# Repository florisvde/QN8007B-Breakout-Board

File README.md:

# QN8007B-Breakout-Board
Breakout board for the Quintic QN8007B single-chip stereo FM transmitter with RDS.

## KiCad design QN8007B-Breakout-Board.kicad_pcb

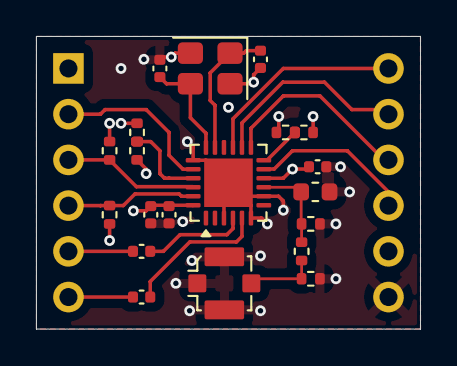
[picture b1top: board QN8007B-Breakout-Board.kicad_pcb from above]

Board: 4 copper layers, 21.3 x 16.3 mm, 22 parts (0 on the bottom side), 19 nets.

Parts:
C1: 10u; C_0402_1005Metric
C2, C7: 100n; C_0402_1005Metric
C3, C4: 10p; C_0402_1005Metric
C5, C6: 4u7; C_0402_1005Metric
J1: U.FL; U.FL_Molex_MCRF_73412-0110_Vertical
J2, J3: Conn_01x06; PinSocket_1x06_P2.54mm_Vertical
L1: 150n; L_0603_1608Metric
R1, R3, R4, R6: DNP; R_0402_1005Metric
R2: 0; R_0402_1005Metric
R5, R7: 100k; R_0402_1005Metric
R9, R10: 10k; R_0402_1005Metric
U1: QN8007B; QFN-24-1EP_4x4mm_P0.5mm_EP2.7x2.7mm
Y1: 26 MHz; Crystal_SMD_Abracon_ABM8G-4Pin_3.2x2.5mm

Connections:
ALI: C5.1, J2.5
ARI: C6.1, J2.6
CEN: J3.4, U1.11 (CEN)
DIN: J2.2, U1.20 (DIN)
GND: C1.2, C2.2, C3.2, C4.2, C7.2, J1.2 (Ext), J3.6, L1.2, R1.2, R3.2, R5.2, R7.2, U1.3 (AUGND), U1.6 (AGND), U1.8 (RFGND), U1.19 (AGND), U1.25 (EP), Y1.2, Y1.4
INT: J3.2, U1.14 (INT)
MCK: J3.3, U1.13 (MCK)
MOD: R4.2, R5.1, U1.12 (MOD)
unnamed: J1.1 (In), R2.2, R3.1
unnamed: C5.2, U1.4 (ALI)
unnamed: C6.2, U1.5 (ARI)
unnamed: L1.1, R1.1, R2.1, U1.9 (RFO)
unnamed: C3.1, U1.17 (XTAL1), Y1.1
unnamed: C4.1, U1.18 (XTAL2), Y1.3
SCL: J2.3, R10.2, U1.22 (SCL)
SDA: J2.4, R9.2, U1.23 (SDA)
SEB: R6.2, R7.1, U1.21 (SEB)
VCC: C1.1, C2.1, C7.1, J3.5, R4.1, R6.1, R9.1, R10.1, U1.10 (VIO), U1.24 (VCC)
WS: J3.1, U1.15 (WS)

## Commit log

2025-10-27 First commit of the schematic.
2026-03-01 Finish routing, small schematic changes to ease routing.
